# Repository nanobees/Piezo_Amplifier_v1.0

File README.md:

# Piezo_Amplifier_v1.0
An Amplifier Designed for Driving Piezo Tubes for Scanning Tunneling Microscope

This amplifier designed for using with a custom STM head. The schematics is based on the B.Sc. Thesis by Burak Budanur.  This circuit needs further testing!(not working!!!) If you have any suggestions or questions please contact with me;
haltugyildirim_at_protonmail.com

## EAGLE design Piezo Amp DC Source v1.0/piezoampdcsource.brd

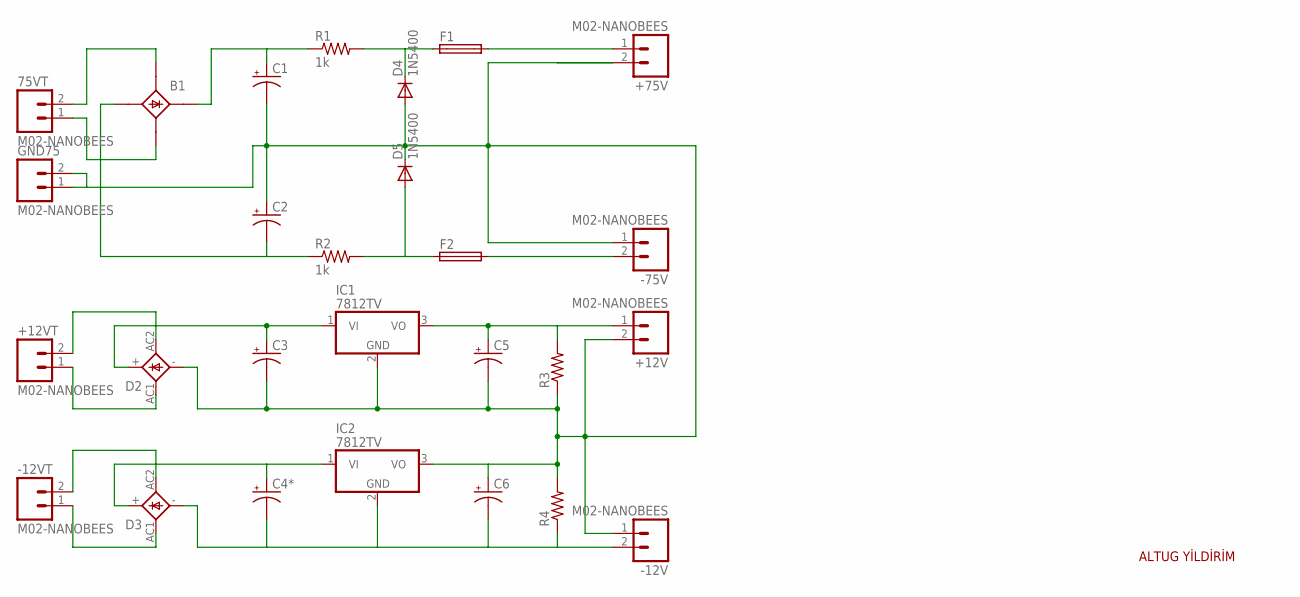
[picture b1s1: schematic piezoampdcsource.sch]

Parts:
75VT: M02-NANOBEES
+12V, +12VT, +75V: M02-NANOBEES
-12V, -12VT, -75V: M02-NANOBEES
B1: B25A-
C1, C2, C3, C4*: CAP_POLPTH3; CPOL-RADIAL-1000UF-63V
C5, C6: CAP_POLPTH2; CPOL-RADIAL-10UF-25V
D2, D3: 2KBP
D4, D5: 1N5400; DO201-15
F1, F2: GSH15
GND75: M02-NANOBEES
IC1, IC2: 7812TV; TO220V
R1, R2: 1k; AXIAL-0.3EZ
R3, R4: RESISTORAXIAL-0.3; AXIAL-0.3

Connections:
GND: +12V.2, +75V.2, -12V.1, -75V.1, C1.2 (-), C2.1 (+), C3.2 (-), C5.2 (-), C6.1 (+), D2.-, D4.A, D5.C, GND75.1, GND75.2, IC1.2 (GND), IC2.3 (VO), R3.P$1 (1), R4.P$2 (2)
unnamed: +12VT.2, D2.AC2
unnamed: 75VT.2, B1.AC1- (AC1)
unnamed: -12VT.2, D3.AC2
unnamed: -12V.2, C4*.2 (-), C6.2 (-), D3.-, IC2.2 (GND), R4.P$1 (1)
unnamed: C4*.1 (+), D3.+, IC2.1 (VI)
unnamed: +12V.1, C5.1 (+), IC1.3 (VO), R3.P$2 (2)
unnamed: +75V.1, F1.2
unnamed: B1.+1 (+), C1.1 (+), R1.P$1 (1)
unnamed: B1.-1 (-), C2.2 (-), R2.P$1 (1)
unnamed: -75V.2, F2.2
unnamed: D4.C, F1.1, R1.P$2 (2)
unnamed: D5.A, F2.1, R2.P$2 (2)
unnamed: +12VT.1, D2.AC1
unnamed: 75VT.1, B1.AC2- (AC2)
unnamed: -12VT.1, D3.AC1
unnamed: C3.1 (+), D2.+, IC1.1 (VI)

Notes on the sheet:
ALTUG YİLDİRİM

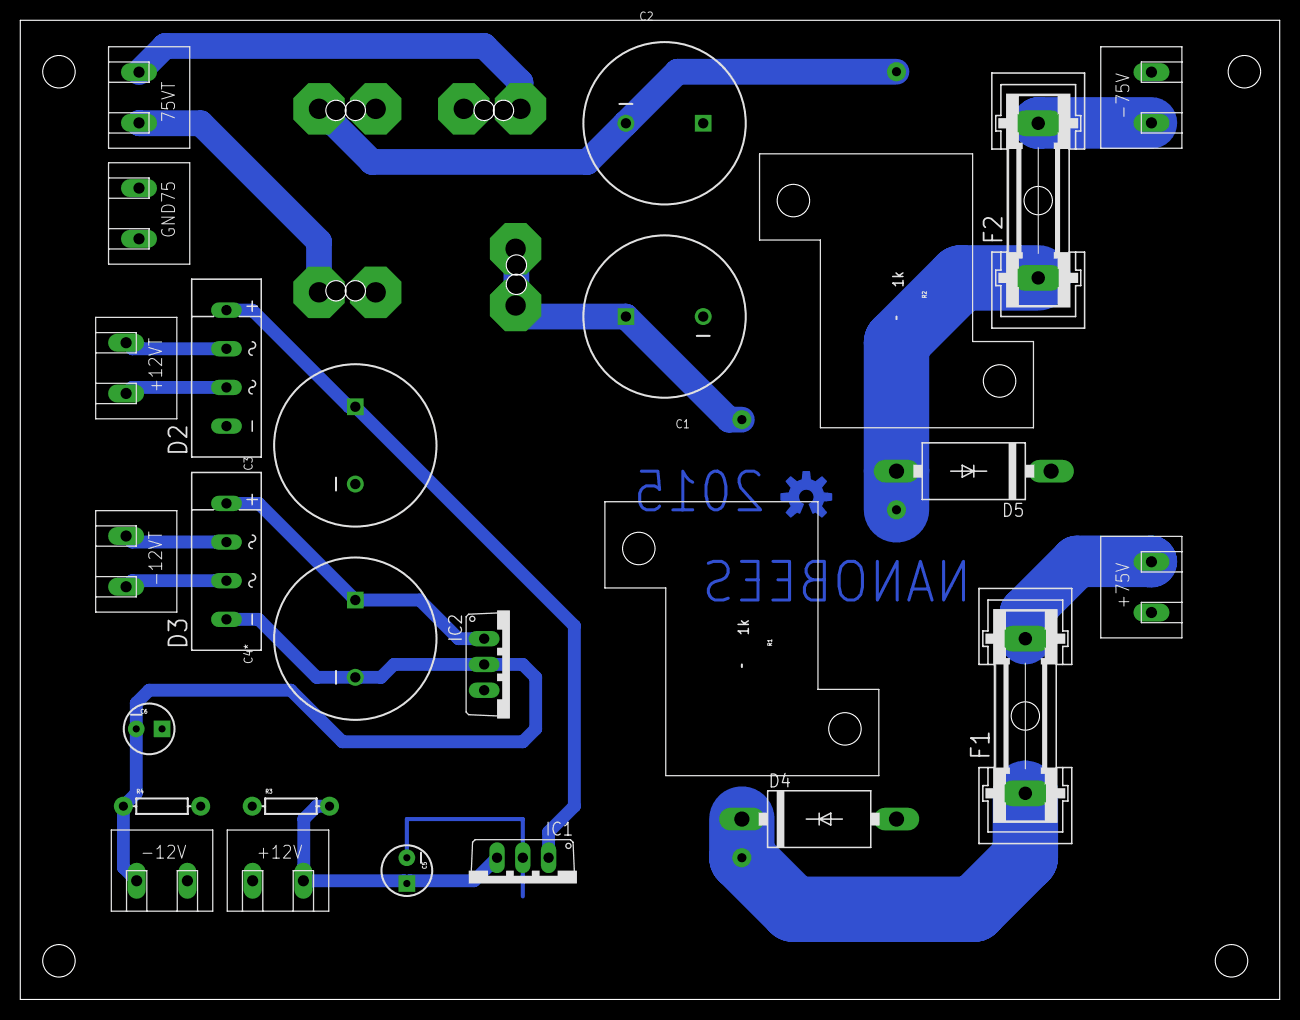
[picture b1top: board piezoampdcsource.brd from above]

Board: 2 copper layers, 124.1 x 96.5 mm, 28 parts (1 on the bottom side), 17 nets.

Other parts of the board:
U$1: OSHW-LOGO-M

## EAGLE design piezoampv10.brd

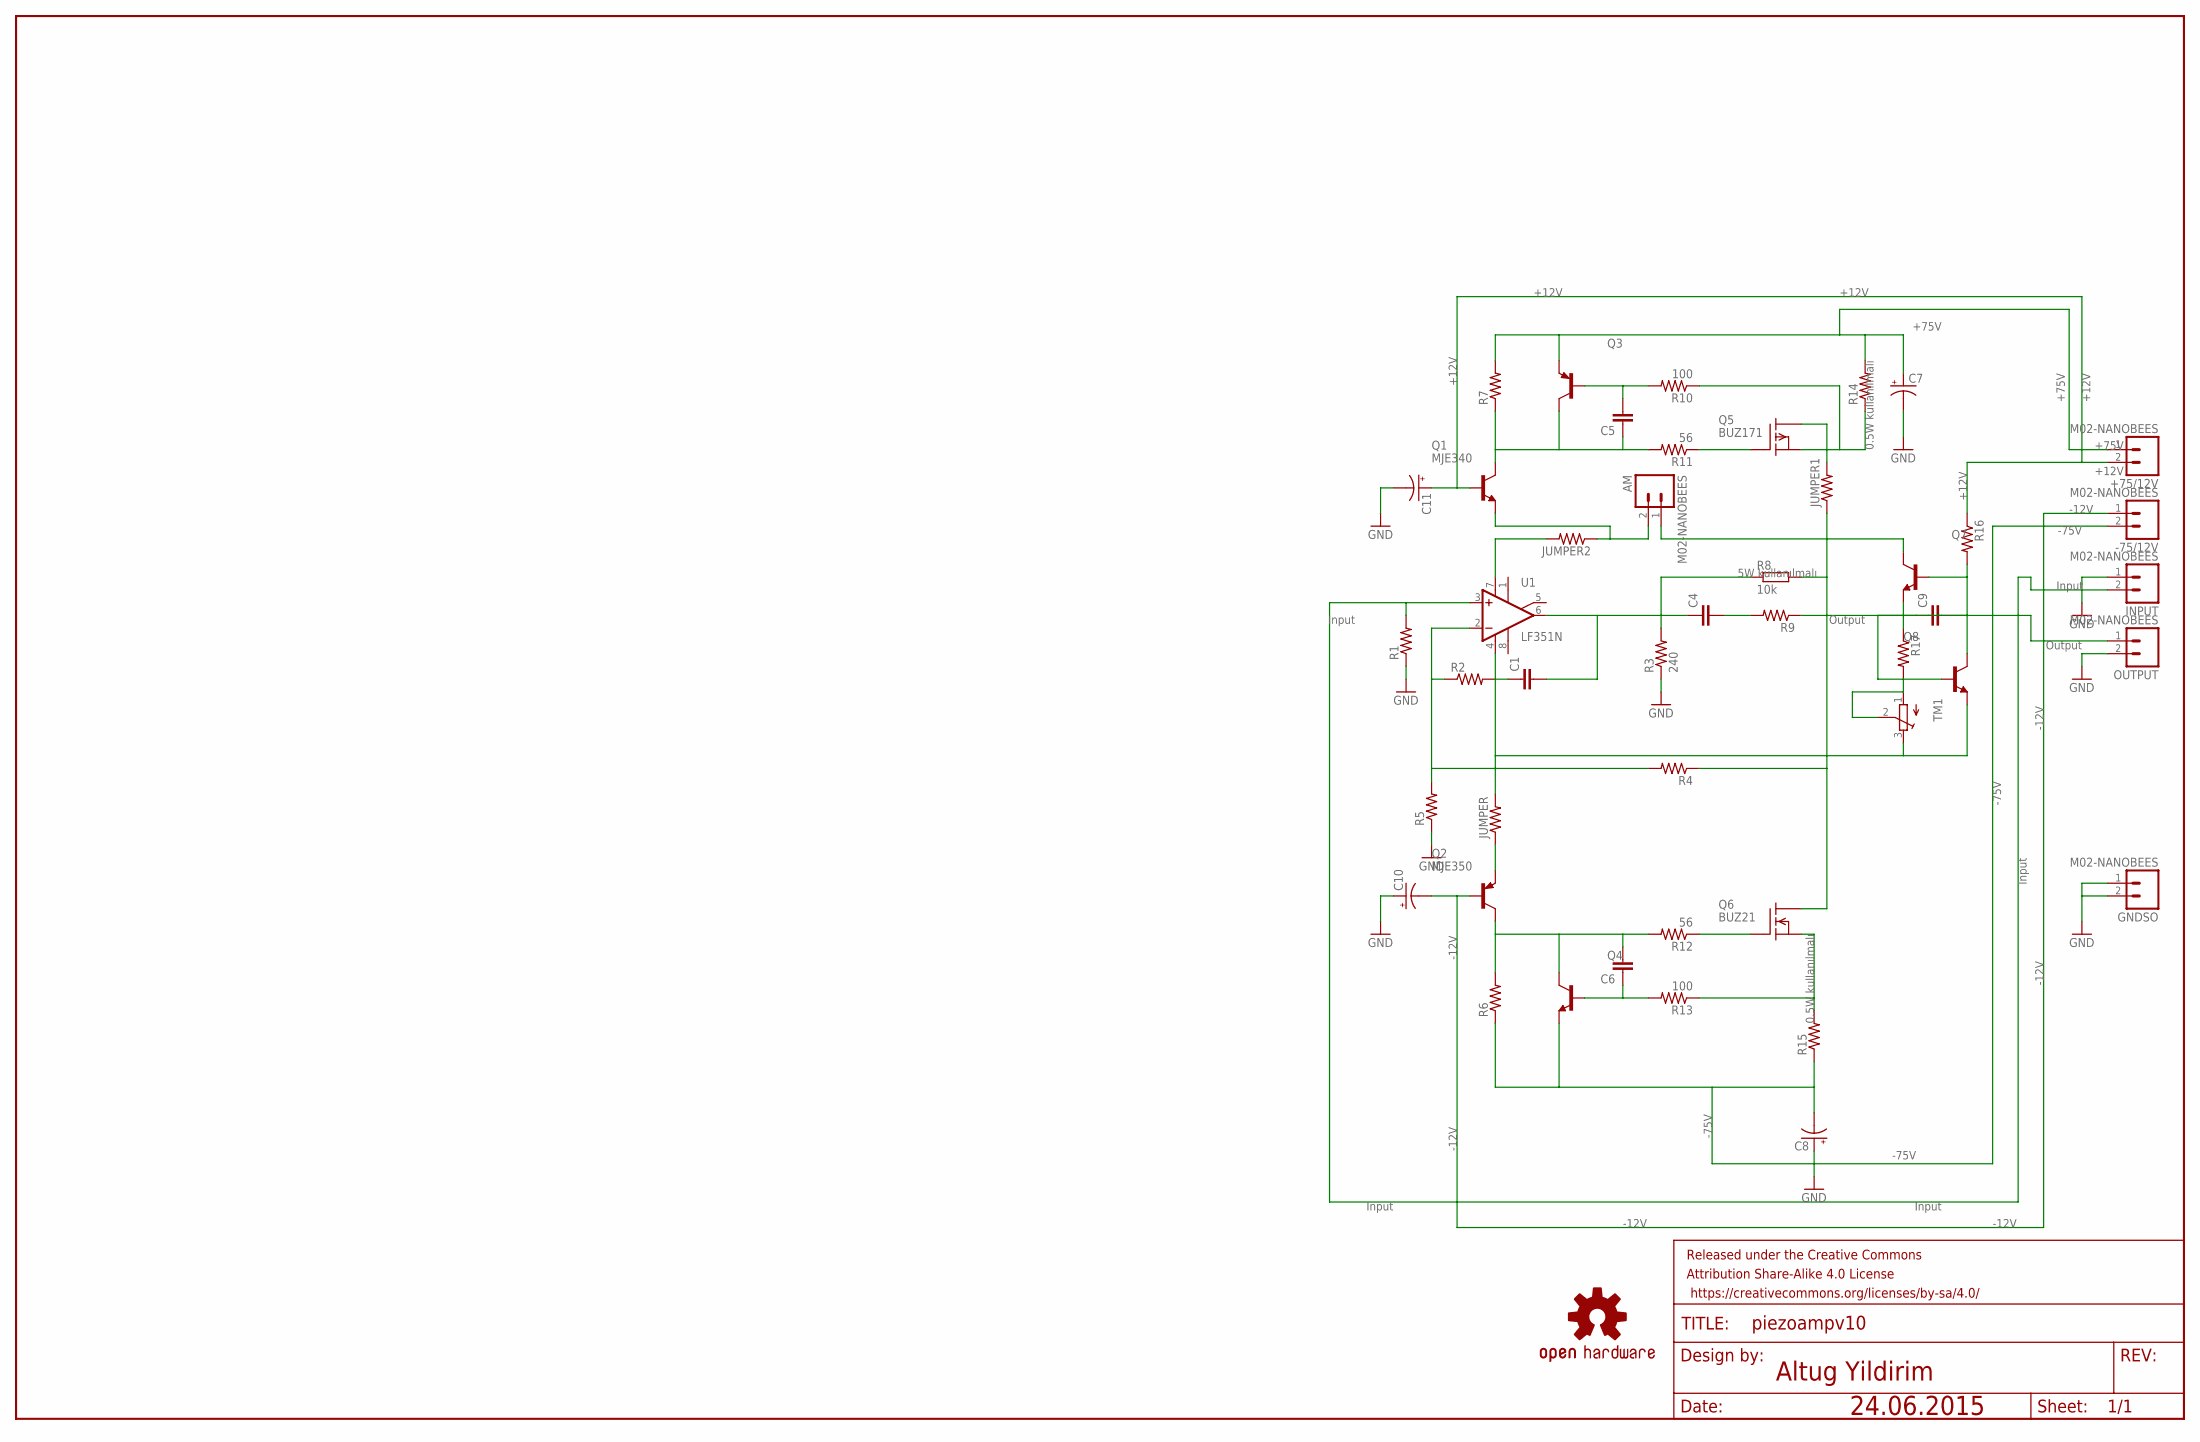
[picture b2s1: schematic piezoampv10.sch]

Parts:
+75/12V: M02-NANOBEES
-75/12V: M02-NANOBEES
AM: M02-NANOBEES
C1, C4, C5, C6, C9: CAPPTH2; CAP-PTH-SMALL2
C7, C8: CAP_POLPTH3; CPOL-RADIAL-1000UF-63V
C10, C11: CAP_POLPTH2; CPOL-RADIAL-10UF-25V
FRAME1: FRAME-LEDGER; CREATIVE_COMMONS
GNDSO: M02-NANOBEES
INPUT: M02-NANOBEES
JUMPER, JUMPER2: R-US_0204/7; 0204/7
JUMPER1: RESISTORPTH-1/4W; AXIAL-0.4
LOGO1: OSHW-LOGOM; OSHW-LOGO-M
OUTPUT: M02-NANOBEES
Q1: MJE340; TO126
Q2: MJE350; TO126
Q3: BF421-PNP-TO92-BCE; TO92-BCE
Q4, Q7, Q8: -NPN-TO92-EBC; TO92-EBC
Q5: BUZ171; TO220
Q6: BUZ21; TO220
R1, R2, R4, R5, R6, R7, R9, R16, R17: R-US_0204/7; 0204/7
R3: 240; 0204/7
R8: 10k; P0817/22
R10, R13: 100; 0204/7
R11, R12: 56; 0204/7
R14, R15: RESISTORPTH-1/2W; AXIAL-0.5
TM1: TRIMPOT3386; TRIM-3386
U1: LF351N; DIL08

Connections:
GND: C7.2 (-), C8.1 (+), C10.1 (+), C11.2 (-), GNDSO.1, GNDSO.2, INPUT.1, OUTPUT.2, R1.1, R3.1, R5.1
unnamed: INPUT.2, R1.2, U1.3 (+IN)
unnamed: R2.1, R4.2, R5.2, U1.2 (-IN)
unnamed: C1.1, R2.2
unnamed: C1.2, C4.1, R3.2, R8.1, U1.6 (OUT)
unnamed: C4.2, R9.2
unnamed: JUMPER.1, Q2.1 (E)
unnamed: JUMPER2.2, U1.7 (V+)
unnamed: -75/12V.1, C10.2 (-), Q2.3 (B)
unnamed: Q5.1 (G), R11.1
unnamed: C6.2, Q2.2 (C), Q4.C, R6.2, R12.2
unnamed: Q6.1 (G), R12.1
unnamed: C6.1, Q4.B, R13.2
unnamed: Q6.3 (S), R13.1, R15.P$2 (2)
unnamed: -75/12V.2, C8.2 (-), Q4.E, R6.1, R15.P$1 (1)
unnamed: C5.1, Q1.2 (C), Q3.C, R7.1, R11.2
unnamed: AM.2, JUMPER2.1, Q1.1 (E)
unnamed: C5.2, Q3.B, R10.2
unnamed: R17.2, TM1.1 (A), TM1.2 (S)
unnamed: Q5.3 (S), R10.1, R14.P$1 (1)
unnamed: +75/12V.1, C7.1 (+), Q3.E, R7.2, R14.P$2 (2)
unnamed: C9.1, Q7.E, Q8.B, R17.1
unnamed: C9.2, Q7.B, Q8.C, R16.2
unnamed: JUMPER1.P$2 (2), Q5.2 (D)
unnamed: OUTPUT.1, R9.1
unnamed: JUMPER1.P$1 (1), Q6.2 (D), R4.1, R8.2
unnamed: +75/12V.2, C11.1 (+), Q1.3 (B), R16.1
unnamed: JUMPER.2, Q8.E, TM1.3 (E), U1.4 (V-)
unnamed: AM.1, Q7.C

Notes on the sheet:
24.06.2015
Altug Yildirim
-12V
+12V
+75V
-75V
Output
Input
0.5W kullanılmalı
5W kullanılmalı

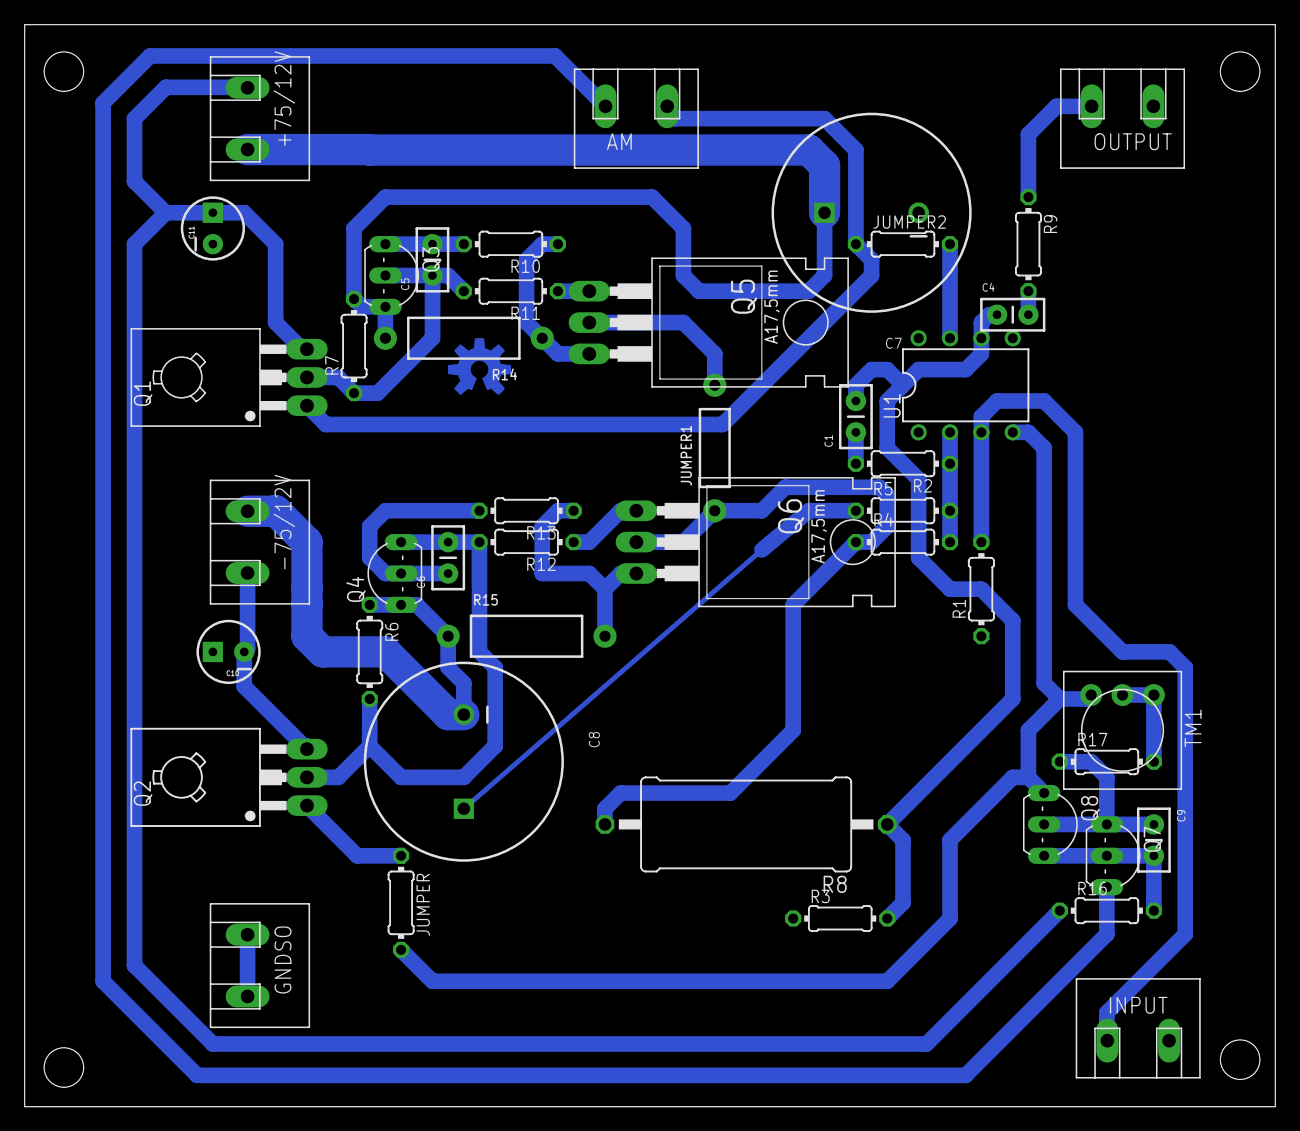
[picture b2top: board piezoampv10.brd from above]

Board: 2 copper layers, 101.3 x 87.6 mm, 47 parts (0 on the bottom side), 29 nets.

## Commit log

2016-08-26 add initial design files
    add initial files

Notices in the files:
parts and their libraries:
SparkFun-Resistors: Licensing: Creative Commons ShareAlike 4.0 International - https://creativecommons.org/licenses/by-sa/4.0
SparkFun-Aesthetics: Released under the Creative Commons Attribution Share-Alike 4.0 License
SparkFun-Aesthetics: https://creativecommons.org/licenses/by-sa/4.0
